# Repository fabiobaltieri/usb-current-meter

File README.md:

USB Current Meter
=================

This is a set of projects used to monitor the power used in an electrical
system using split core current sensors.

Project page on:

http://fabiobaltieri.com/2012/08/09/usb-current-meter/

License
-------

This program is free software: you can redistribute it and/or modify
it under the terms of the GNU General Public License as published by
the Free Software Foundation, either version 2 of the License, or
(at your option) any later version.

Contents
--------

    COPYING        text version of the GPL
    README         this file
    bootloader-8x/ source directory for 8x version bootloader
    commandline/   source directory for the commandline utility
    firmware*/     source directory for firmware files
    hardware/      source directory for the hardware design files
    rrd/           script and examples for usage with rrdtool

Firmware
--------

Building requires an avr-gcc toolchain, in the firmware/ directory, to build
run:

    make main.hex

Flashing the firmware on the device requires avrdude and a compatible hardware
programmer. Default configuration is stored at the beginning of the Makefile.
To program with the default configuration, run:

    make flash

Fuses can be configured running:

    make fuses

Hardware
--------

All hardware files (schematic, layout and libraries) are in CadSoft Eagle 6
format.

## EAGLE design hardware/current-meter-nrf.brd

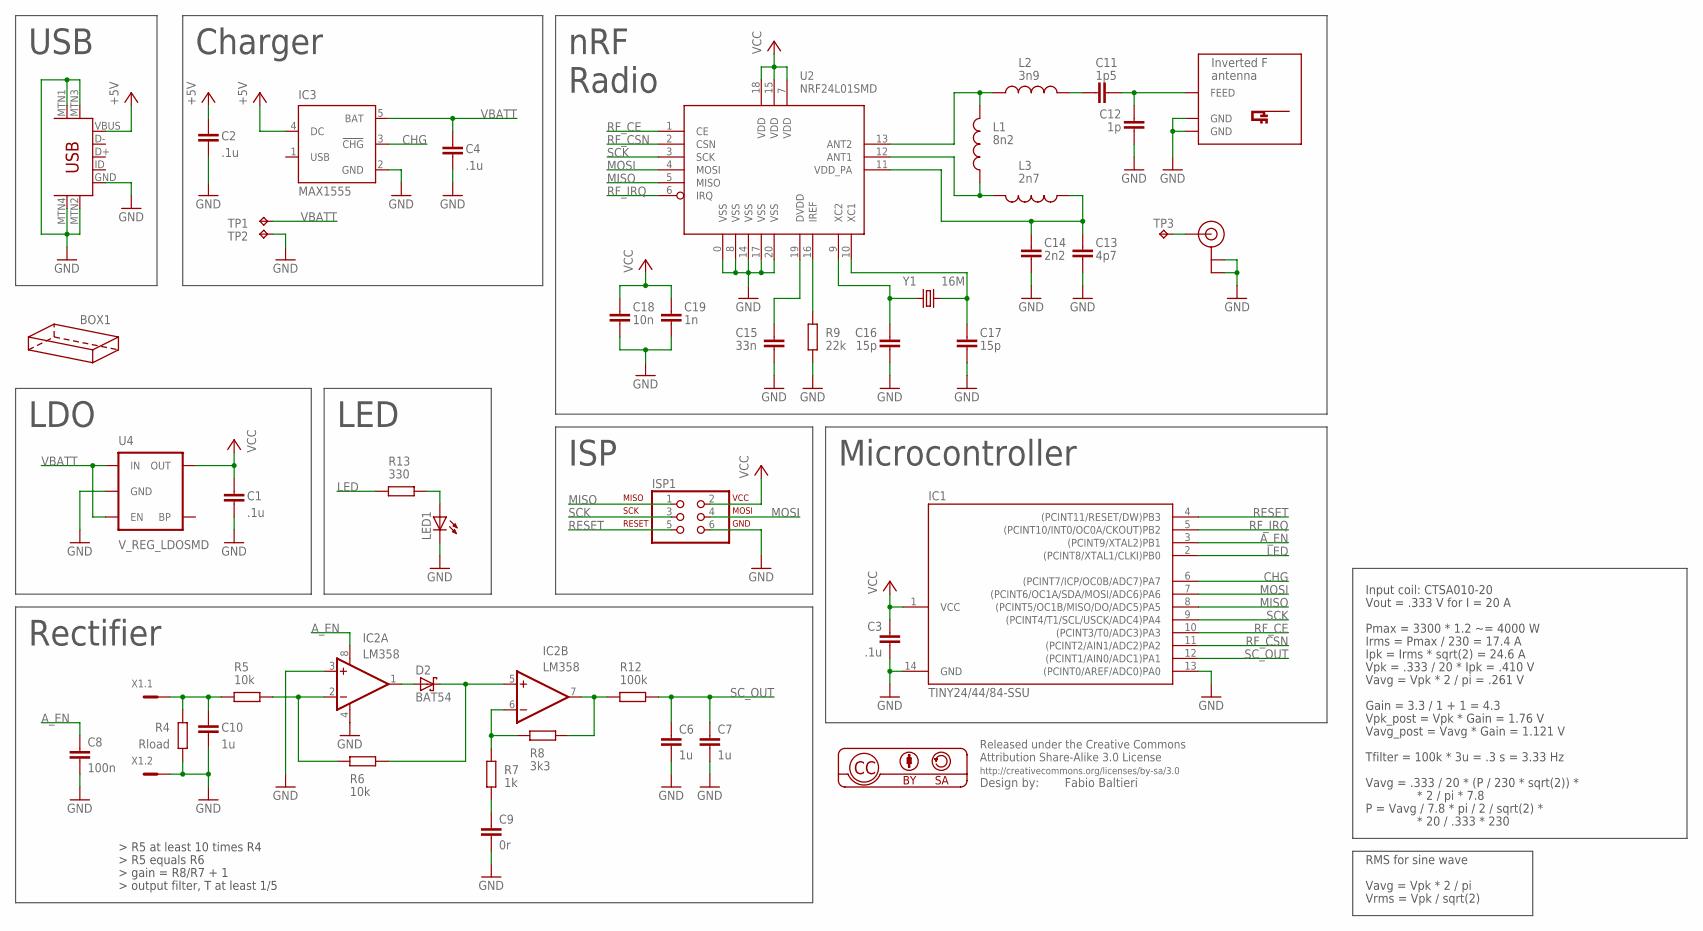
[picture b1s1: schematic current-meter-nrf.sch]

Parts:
BOX1: HAMMOND-BOX-G-1H; 1551G-1HOLE
C1, C2, C3, C4: .1u; C0805
C6, C7, C10: 1u; C0805
C8: 100n; C0805
C9: 0r; C0805
C11: 1p5; C0603
C12: 1p; C0603
C13: 4p7; C0603
C14: 2n2; C0603
C15: 33n; C0603
C16, C17: 15p; C0603
C18: 10n; C0603
C19: 1n; C0603
D2: BAT54; SOT23
IC1: TINY24/44/84-SSU; SOIC14
IC2: LM358; SO08
IC3: MAX1555; SOT23-5L
ISP1: ISP-AVR910PTH; 2X03
L1: 8n2; 0603
L2: 3n9; 0603
L3: 2n7; 0603
LED1: LEDSML0805; SML0805
R4: Rload; R0805
R5, R6: 10k; R0603
R7: 1k; R0603
R8: 3k3; R0603
R9: 22k; R0603
R12: 100k; R0603
R13: 330; R0603
TP1, TP2: TPTP12R; TP12R
TP3: TPTP08SQ; TP08SQ
U2: NRF24L01SMD; QFN20
U3: USB-MINIB-5PIN; USB-MINIB
U4: V_REG_LDOSMD; SOT23-5
U$1: INVERTED_F_ANTENNA+5; DN007+5
U$2: U.FL
X1: MC2
Y1: 16M; CRYSTAL-SMD-5X3

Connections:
+5V: C2.1, IC3.4 (DC), U3.VBUS
A_EN: C8.1, IC1.3 ((PCINT9/XTAL2)PB1), IC2.8 (V+)
CHG: IC1.6 ((PCINT7/ICP/OC0B/ADC7)PA7), IC3.3 (!CHG)
GND: C1.2, C2.2, C3.2, C4.2, C6.2, C7.2, C8.2, C9.2, C10.2, C12.2, C13.2, C14.2, C15.2, C16.2, C17.2, C18.2, C19.2, IC1.13 ((PCINT0/AREF/ADC0)PA0), IC1.14 (GND), IC2.3 (+IN), IC2.4 (V-), IC3.2 (GND), ISP1.6, LED1.C, R4.1, R9.2, TP2.TP, U2.0 (VSS), U2.8 (VSS), U2.14 (VSS), U2.17 (VSS), U2.20 (VSS), U3.GND, U3.MTN1 (MTN2), U3.MTN2 (MTN3), U3.MTN3 (MTN1), U3.MTN4, U4.2 (GND), U$1.GND, U$1.GND@1 (GND), U$2.P$1 (GND), U$2.P$2 (GND), X1.2
LED: IC1.2 ((PCINT8/XTAL1/CLKI)PB0), R13.2
MISO: IC1.8 ((PCINT5/OC1B/MISO/DO/ADC5)PA5), ISP1.1, U2.5 (MISO)
MOSI: IC1.7 ((PCINT6/OC1A/SDA/MOSI/ADC6)PA6), ISP1.4, U2.4 (MOSI)
unnamed: LED1.A, R13.1
unnamed: C9.1, R7.1
unnamed: L1.2, L3.2, U2.12 (ANT1)
unnamed: L1.1, L2.1, U2.13 (ANT2)
unnamed: IC2.2 (-IN), R5.2, R6.1
unnamed: D2.1 (A), IC2.1 (OUT)
unnamed: D2.3 (C), IC2.5 (+IN), R6.2
unnamed: C11.1, L2.2
unnamed: IC2.6 (-IN), R7.2, R8.1
unnamed: IC2.7 (OUT), R8.2, R12.1
unnamed: C11.2, C12.1, U$1.FEED
unnamed: C13.1, C14.1, L3.1, U2.11 (VDD_PA)
unnamed: C15.1, U2.19 (DVDD)
unnamed: R9.1, U2.16 (IREF)
unnamed: C17.1, U2.10 (XC1), Y1.3 (2)
unnamed: C16.1, U2.9 (XC2), Y1.1
unnamed: TP3.TP, U$2.P$3 (SIGNAL)
RESET: IC1.4 ((PCINT11/RESET/DW)PB3), ISP1.5
RF_CE: IC1.10 ((PCINT3/T0/ADC3)PA3), U2.1 (CE)
RF_CSN: IC1.11 ((PCINT2/AIN1/ADC2)PA2), U2.2 (CSN)
RF_IRQ: IC1.5 ((PCINT10/INT0/OC0A/CKOUT)PB2), U2.6 (IRQ)
SCK: IC1.9 ((PCINT4/T1/SCL/USCK/ADC4)PA4), ISP1.3, U2.3 (SCK)
SC_IN_A: C10.1, R4.2, R5.1, X1.1
SC_OUT: C6.1, C7.1, IC1.12 ((PCINT1/AIN0/ADC1)PA1), R12.2
VBATT: C4.1, IC3.5 (BAT), TP1.TP, U4.1 (IN), U4.3 (EN)
VCC: C1.1, C3.1, C18.1, C19.1, IC1.1 (VCC), ISP1.2, U2.7 (VDD), U2.15 (VDD), U2.18 (VDD), U4.5 (OUT)

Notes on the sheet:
USB
Microcontroller
ISP
LED
Rectifier
Pmax = 3300 * 1.2 ~= 4000 W
Irms = Pmax / 230 = 17.4 A
Ipk = Irms * sqrt(2) = 24.6 A
Vpk = .333 / 20 * Ipk = .410 V
Vout = .333 V for I = 20 A
Input coil: CTSA010-20
Vavg = Vpk * 2 / pi = .261 V
Gain = 3.3 / 1 + 1 = 4.3
Vpk_post = Vpk * Gain = 1.76 V
Vavg_post = Vavg * Gain = 1.121 V
RMS for sine wave
Vavg = Vpk * 2 / pi
Vrms = Vpk / sqrt(2)
Tfilter = 100k * 3u = .3 s = 3.33 Hz
Vavg = .333 / 20 * (P / 230 * sqrt(2)) *
* 2 / pi * 7.8
P = Vavg / 7.8 * pi / 2 / sqrt(2) *
* 20 / .333 * 230
nRF
Charger
Radio
LDO

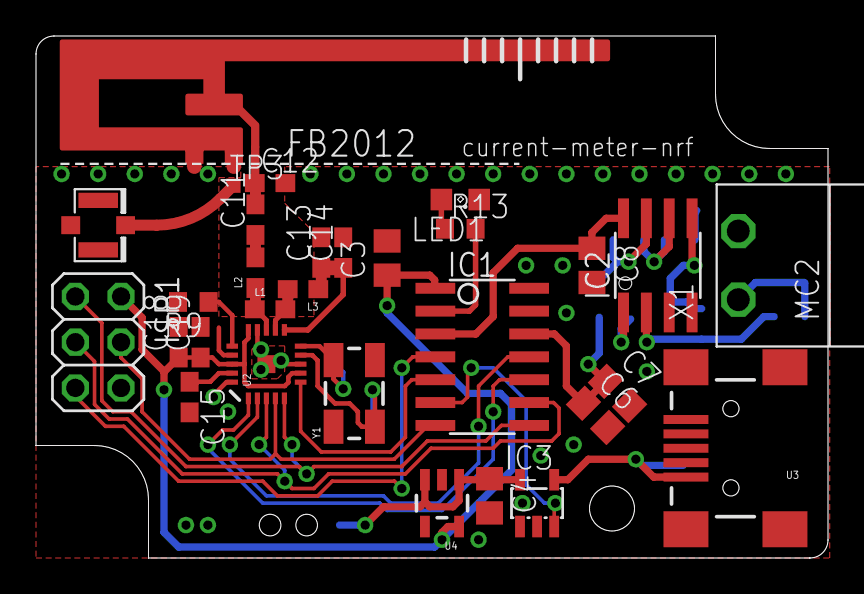
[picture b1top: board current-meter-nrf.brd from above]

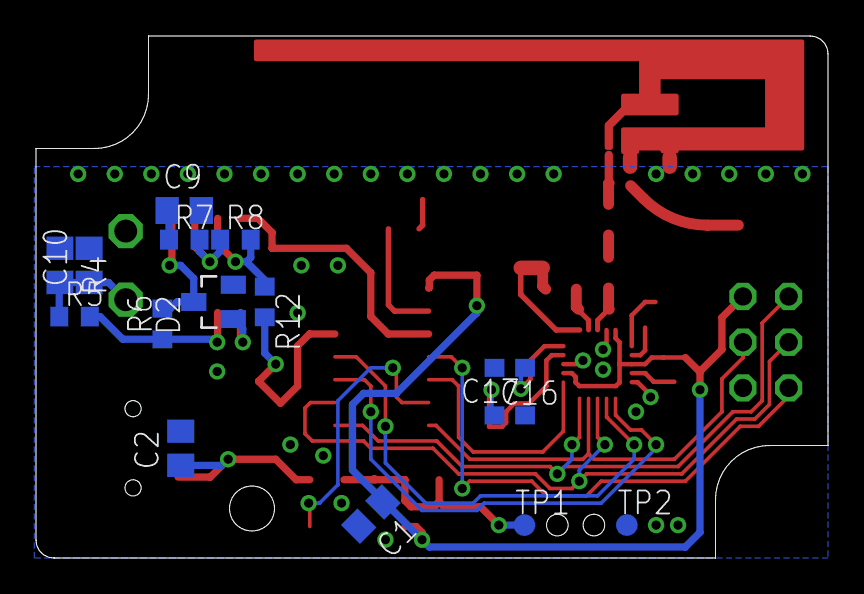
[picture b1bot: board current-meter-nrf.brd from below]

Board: 2 copper layers, 44.0 x 29.0 mm, 46 parts (15 on the bottom side), 33 nets.

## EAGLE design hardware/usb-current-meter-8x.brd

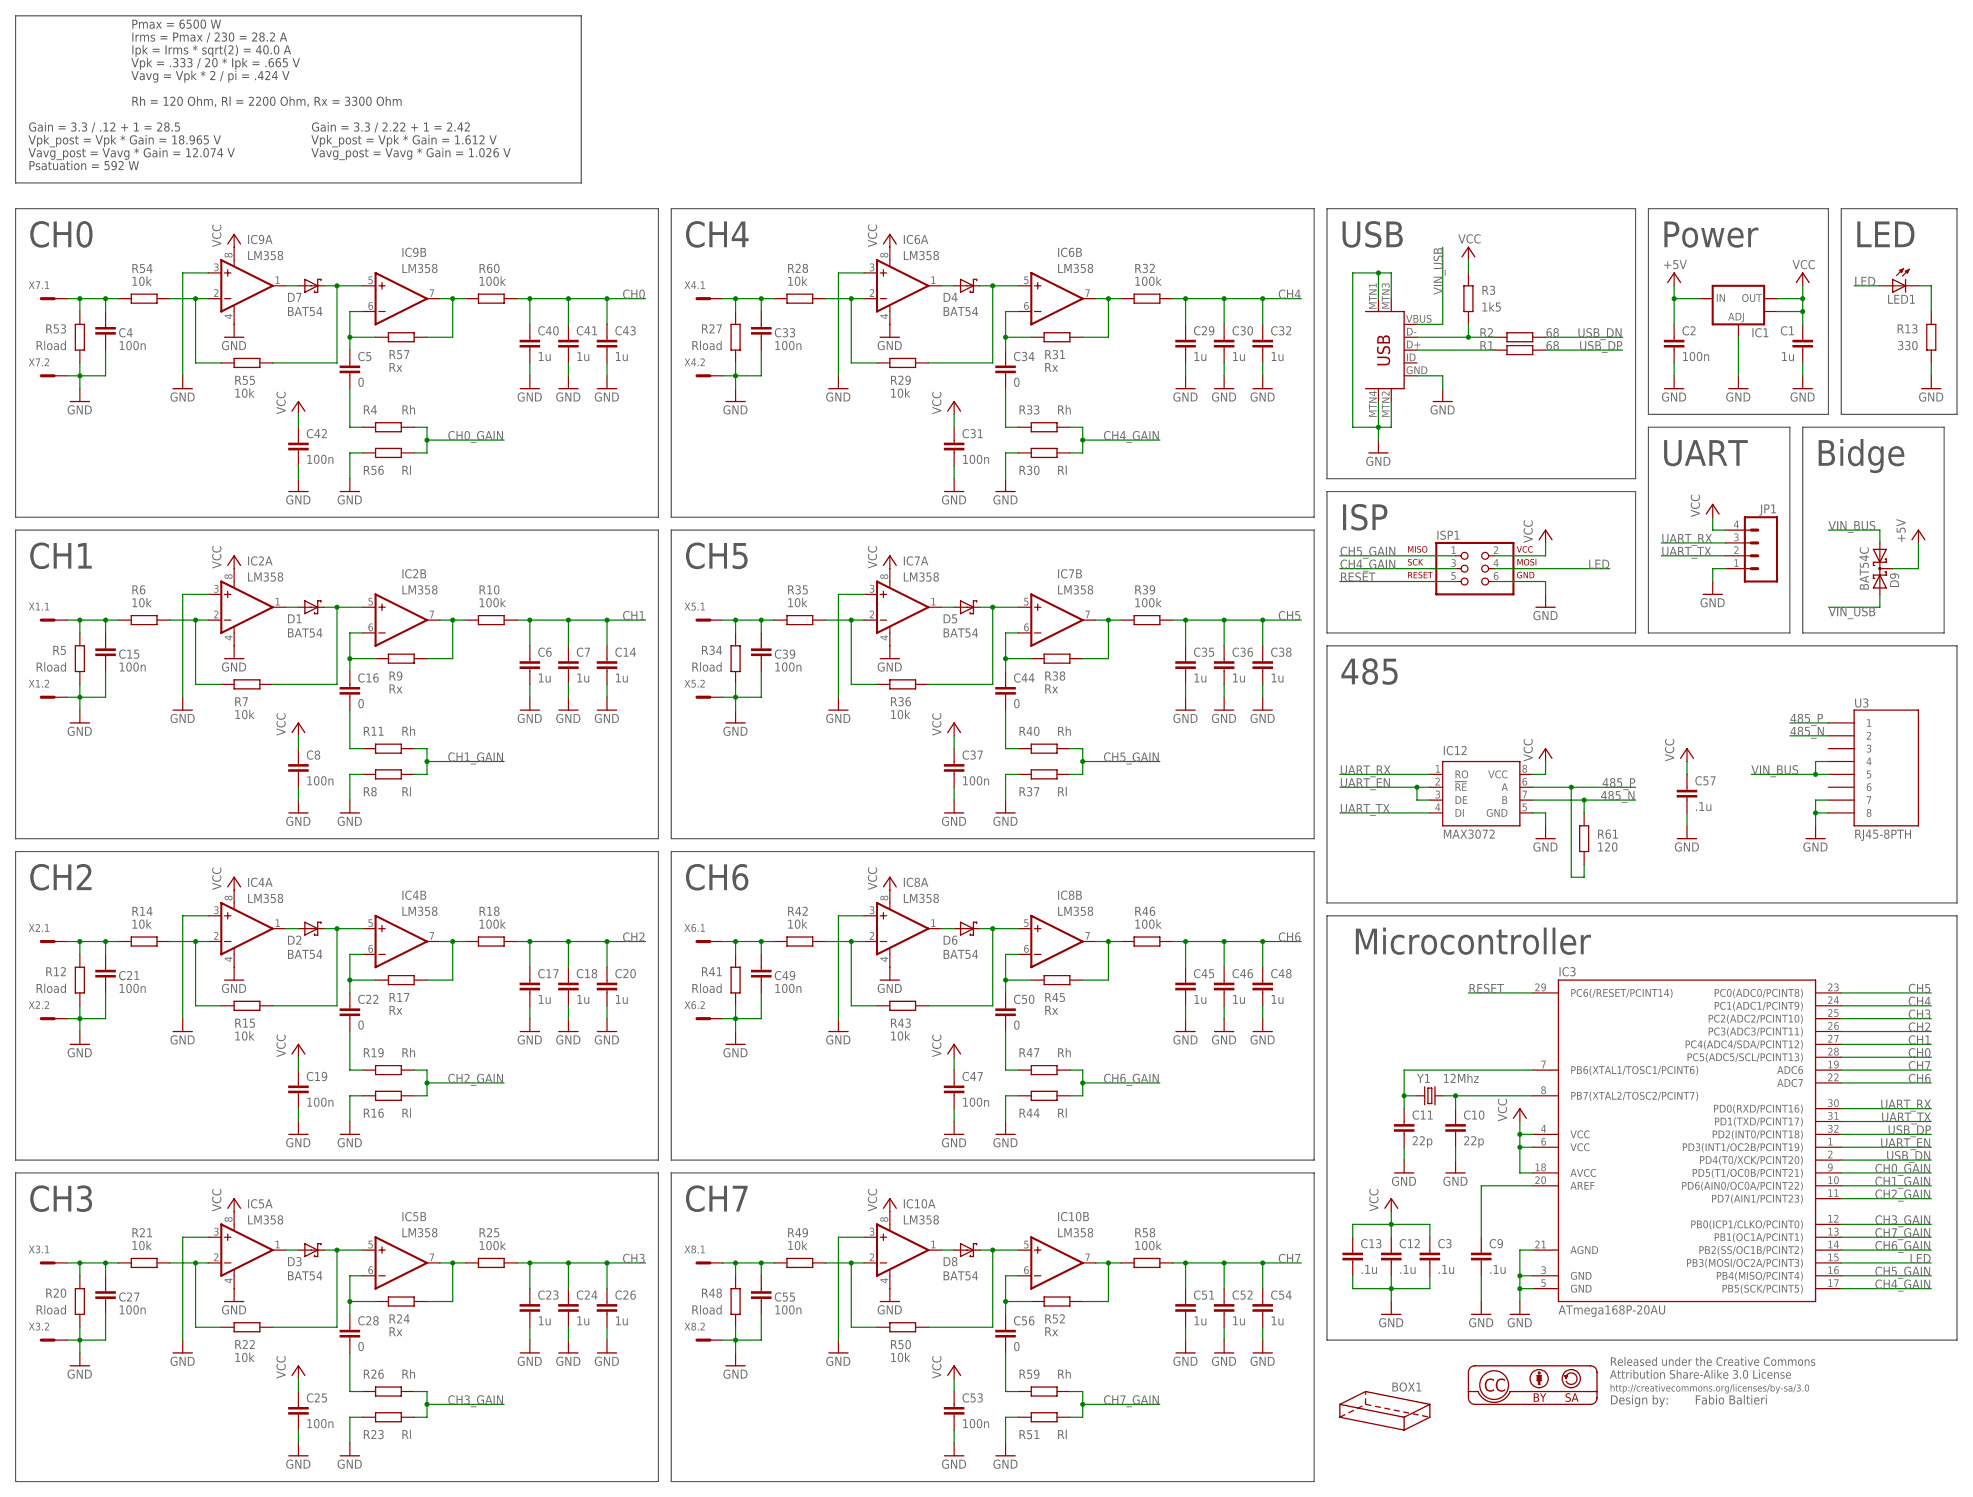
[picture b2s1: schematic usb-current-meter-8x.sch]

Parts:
BOX1: HAMMOND-BOX-XXA; 1591XXA
C1, C6, C7, C14, C17, C18, C20, C23, C24, C26, C29, C30, C32, C35, C36, C38, C40, C41, C43, C45, C46, C48, C51, C52, C54: 1u; C0805
C2, C4, C8, C15, C19, C21, C25, C27, C31, C33, C37, C39, C42, C47, C49, C53, C55: 100n; C0805
C3, C9, C12, C13, C57: .1u; C0805
C5, C16, C22, C28, C34, C44, C50, C56: 0; C0805
C10, C11: 22p; C0805
D1, D2, D3, D4, D5, D6, D7, D8: BAT54; SOT23
D9: BAT54C; SOT23
IC1: V_REG_LM1117SOT223; SOT223
IC2, IC4, IC5, IC6, IC7, IC8, IC9, IC10: LM358; SO08
IC3: ATmega168P-20AU; TQFP32-08
IC12: MAX3072; SOIC8
ISP1: ISP-AVR910PTH; 2X03
JP1: M04PTH; 1X04
LED1: LEDSML0805; SML0805
R1, R2: 68; R0603
R3: 1k5; R0603
R4, R11, R19, R26, R33, R40, R47, R59: Rh; R0603
R5, R12, R20, R27, R34, R41, R48, R53: Rload; R0805
R6, R7, R14, R15, R21, R22, R28, R29, R35, R36, R42, R43, R49, R50, R54, R55: 10k; R0603
R8, R16, R23, R30, R37, R44, R51, R56: Rl; R0603
R9, R17, R24, R31, R38, R45, R52, R57: Rx; R0603
R10, R18, R25, R32, R39, R46, R58, R60: 100k; R0603
R13: 330; R0603
R61: 120; R0603
U3: RJ45-8PTH; RJ45-8
U$1: USB-MINIB-5PIN; USB-MINIB
U$2: Fabio Baltieri; CREATIVE_COMMONS
X1, X2, X3, X4, X5, X6, X7, X8: MC2
Y1: 12Mhz; HC49U-V

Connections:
485_N: IC12.7 (B), R61.1, U3.2
485_P: IC12.6 (A), R61.2, U3.1
+5V: C2.1, D9.3 (CC), IC1.3 (IN)
CH0: C40.1, C41.1, C43.1, IC3.28 (PC5(ADC5/SCL/PCINT13)), R60.2
CH0_GAIN: IC3.9 (PD5(T1/OC0B/PCINT21)), R4.1, R56.2
CH0_IN: C4.1, R53.2, R54.1, X7.1
CH0_IN1: C15.1, R5.2, R6.1, X1.1
CH0_IN2: C21.1, R12.2, R14.1, X2.1
CH0_IN3: C33.1, R27.2, R28.1, X4.1
CH0_IN4: C39.1, R34.2, R35.1, X5.1
CH0_IN5: C55.1, R48.2, R49.1, X8.1
CH0_IN6: C27.1, R20.2, R21.1, X3.1
CH0_IN8: C49.1, R41.2, R42.1, X6.1
CH1: C6.1, C7.1, C14.1, IC3.27 (PC4(ADC4/SDA/PCINT12)), R10.2
CH1_GAIN: IC3.10 (PD6(AIN0/OC0A/PCINT22)), R8.2, R11.1
CH2: C17.1, C18.1, C20.1, IC3.26 (PC3(ADC3/PCINT11)), R18.2
CH2_GAIN: IC3.11 (PD7(AIN1/PCINT23)), R16.2, R19.1
CH3: C23.1, C24.1, C26.1, IC3.25 (PC2(ADC2/PCINT10)), R25.2
CH3_GAIN: IC3.12 (PB0(ICP1/CLKO/PCINT0)), R23.2, R26.1
CH4: C29.1, C30.1, C32.1, IC3.24 (PC1(ADC1/PCINT9)), R32.2
CH4_GAIN: IC3.17 (PB5(SCK/PCINT5)), ISP1.3, R30.2, R33.1
CH5: C35.1, C36.1, C38.1, IC3.23 (PC0(ADC0/PCINT8)), R39.2
CH5_GAIN: IC3.16 (PB4(MISO/PCINT4)), ISP1.1, R37.2, R40.1
CH6: C45.1, C46.1, C48.1, IC3.22 (ADC7), R46.2
CH6_GAIN: IC3.14 (PB2(SS/OC1B/PCINT2)), R44.2, R47.1
CH7: C51.1, C52.1, C54.1, IC3.19 (ADC6), R58.2
CH7_GAIN: IC3.13 (PB1(OC1A/PCINT1)), R51.2, R59.1
GND: C1.2, C2.2, C3.2, C4.2, C6.2, C7.2, C8.2, C9.2, C10.2, C11.2, C12.2, C13.2, C14.2, C15.2, C17.2, C18.2, C19.2, C20.2, C21.2, C23.2, C24.2, C25.2, C26.2, C27.2, C29.2, C30.2, C31.2, C32.2, C33.2, C35.2, C36.2, C37.2, C38.2, C39.2, C40.2, C41.2, C42.2, C43.2, C45.2, C46.2, C47.2, C48.2, C49.2, C51.2, C52.2, C53.2, C54.2, C55.2, C57.2, IC1.1 (ADJ), IC2.3 (+IN), IC2.4 (V-), IC3.3 (GND), IC3.5 (GND), IC3.21 (AGND), IC4.3 (+IN), IC4.4 (V-), IC5.3 (+IN), IC5.4 (V-), IC6.3 (+IN), IC6.4 (V-), IC7.3 (+IN), IC7.4 (V-), IC8.3 (+IN), IC8.4 (V-), IC9.3 (+IN), IC9.4 (V-), IC10.3 (+IN), IC10.4 (V-), IC12.5 (GND), ISP1.6, JP1.1, R5.1, R8.1, R12.1, R13.1, R16.1, R20.1, R23.1, R27.1, R30.1, R34.1, R37.1, R41.1, R44.1, R48.1, R51.1, R53.1, R56.1, U3.7, U3.8, U$1.GND, U$1.MTN1 (MTN2), U$1.MTN2 (MTN3), U$1.MTN3 (MTN1), U$1.MTN4, X1.2, X2.2, X3.2, X4.2, X5.2, X6.2, X7.2, X8.2
LED: IC3.15 (PB3(MOSI/OC2A/PCINT3)), ISP1.4, LED1.A
unnamed: R2.1, R3.1, U$1.D-
unnamed: R1.1, U$1.D+
unnamed: LED1.C, R13.2
unnamed: C11.1, IC3.7 (PB6(XTAL1/TOSC1/PCINT6)), Y1.1
unnamed: C10.1, IC3.8 (PB7(XTAL2/TOSC2/PCINT7)), Y1.2
unnamed: C9.1, IC3.20 (AREF)
unnamed: C5.2, R4.2
unnamed: IC2.2 (-IN), R6.2, R7.1
unnamed: D1.1 (A), IC2.1 (OUT)
unnamed: D1.3 (C), IC2.5 (+IN), R7.2
unnamed: C16.1, IC2.6 (-IN), R9.1
unnamed: IC2.7 (OUT), R9.2, R10.1
unnamed: C16.2, R11.2
unnamed: IC4.2 (-IN), R14.2, R15.1
unnamed: D2.1 (A), IC4.1 (OUT)
unnamed: D2.3 (C), IC4.5 (+IN), R15.2
unnamed: C22.1, IC4.6 (-IN), R17.1
unnamed: IC4.7 (OUT), R17.2, R18.1
unnamed: C22.2, R19.2
unnamed: IC6.2 (-IN), R28.2, R29.1
unnamed: D4.1 (A), IC6.1 (OUT)
unnamed: D4.3 (C), IC6.5 (+IN), R29.2
unnamed: C34.1, IC6.6 (-IN), R31.1
unnamed: IC6.7 (OUT), R31.2, R32.1
unnamed: C34.2, R33.2
unnamed: IC7.2 (-IN), R35.2, R36.1
unnamed: D5.1 (A), IC7.1 (OUT)
unnamed: D5.3 (C), IC7.5 (+IN), R36.2
unnamed: C44.1, IC7.6 (-IN), R38.1
unnamed: IC7.7 (OUT), R38.2, R39.1
unnamed: C44.2, R40.2
unnamed: IC10.2 (-IN), R49.2, R50.1
unnamed: D8.1 (A), IC10.1 (OUT)
unnamed: D8.3 (C), IC10.5 (+IN), R50.2
unnamed: C56.1, IC10.6 (-IN), R52.1
unnamed: IC10.7 (OUT), R52.2, R58.1
unnamed: IC9.2 (-IN), R54.2, R55.1
unnamed: D7.1 (A), IC9.1 (OUT)
unnamed: D7.3 (C), IC9.5 (+IN), R55.2
unnamed: C5.1, IC9.6 (-IN), R57.1
unnamed: IC9.7 (OUT), R57.2, R60.1
unnamed: C56.2, R59.2
unnamed: IC5.2 (-IN), R21.2, R22.1
unnamed: D3.1 (A), IC5.1 (OUT)
unnamed: D3.3 (C), IC5.5 (+IN), R22.2
unnamed: C28.1, IC5.6 (-IN), R24.1
unnamed: IC5.7 (OUT), R24.2, R25.1
unnamed: C28.2, R26.2
unnamed: IC8.2 (-IN), R42.2, R43.1
unnamed: D6.1 (A), IC8.1 (OUT)
unnamed: D6.3 (C), IC8.5 (+IN), R43.2
unnamed: C50.1, IC8.6 (-IN), R45.1
unnamed: IC8.7 (OUT), R45.2, R46.1
unnamed: C50.2, R47.2
RESET: IC3.29 (PC6(/RESET/PCINT14)), ISP1.5
UART_EN: IC3.1 (PD3(INT1/OC2B/PCINT19)), IC12.2 (!RE), IC12.3 (DE)
UART_RX: IC3.30 (PD0(RXD/PCINT16)), IC12.1 (RO), JP1.3
UART_TX: IC3.31 (PD1(TXD/PCINT17)), IC12.4 (DI), JP1.2
USB_DN: IC3.2 (PD4(T0/XCK/PCINT20)), R2.2
USB_DP: IC3.32 (PD2(INT0/PCINT18)), R1.2
VCC: C1.1, C3.1, C8.1, C12.1, C13.1, C19.1, C25.1, C31.1, C37.1, C42.1, C47.1, C53.1, C57.1, IC1.2 (OUT), IC1.4 (OUT), IC2.8 (V+), IC3.4 (VCC), IC3.6 (VCC), IC3.18 (AVCC), IC4.8 (V+), IC5.8 (V+), IC6.8 (V+), IC7.8 (V+), IC8.8 (V+), IC9.8 (V+), IC10.8 (V+), IC12.8 (VCC), ISP1.2, JP1.4, R3.2
VIN_BUS: D9.1 (A1), U3.4, U3.5
VIN_USB: D9.2 (A2), U$1.VBUS

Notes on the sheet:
USB
Power
Microcontroller
ISP
LED
CH0
UART
CH1
CH2
CH3
CH4
CH5
CH6
CH7
485
Bidge
Pmax = 6500 W
Irms = Pmax / 230 = 28.2 A
Ipk = Irms * sqrt(2) = 40.0 A
Vpk = .333 / 20 * Ipk = .665 V
Vavg = Vpk * 2 / pi = .424 V
Gain = 3.3 / .12 + 1 = 28.5
Vpk_post = Vpk * Gain = 18.965 V
Vavg_post = Vavg * Gain = 12.074 V
Rh = 120 Ohm, Rl = 2200 Ohm, Rx = 3300 Ohm
Gain = 3.3 / 2.22 + 1 = 2.42
Vpk_post = Vpk * Gain = 1.612 V
Vavg_post = Vavg * Gain = 1.026 V
Psatuation = 592 W

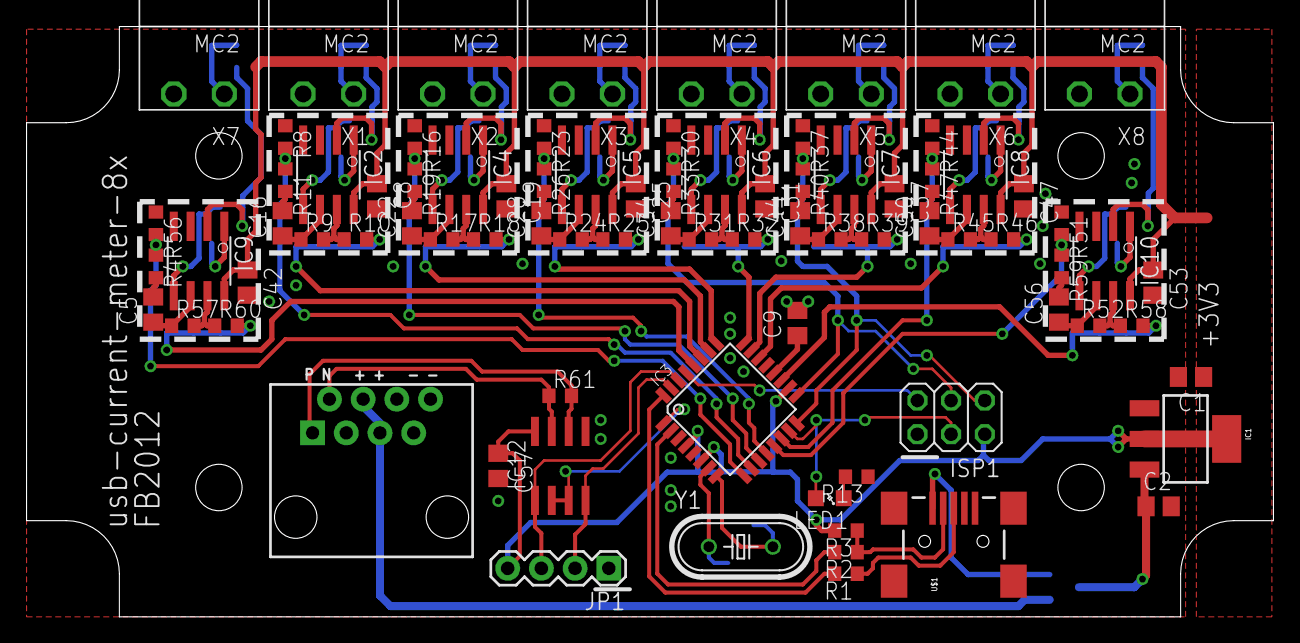
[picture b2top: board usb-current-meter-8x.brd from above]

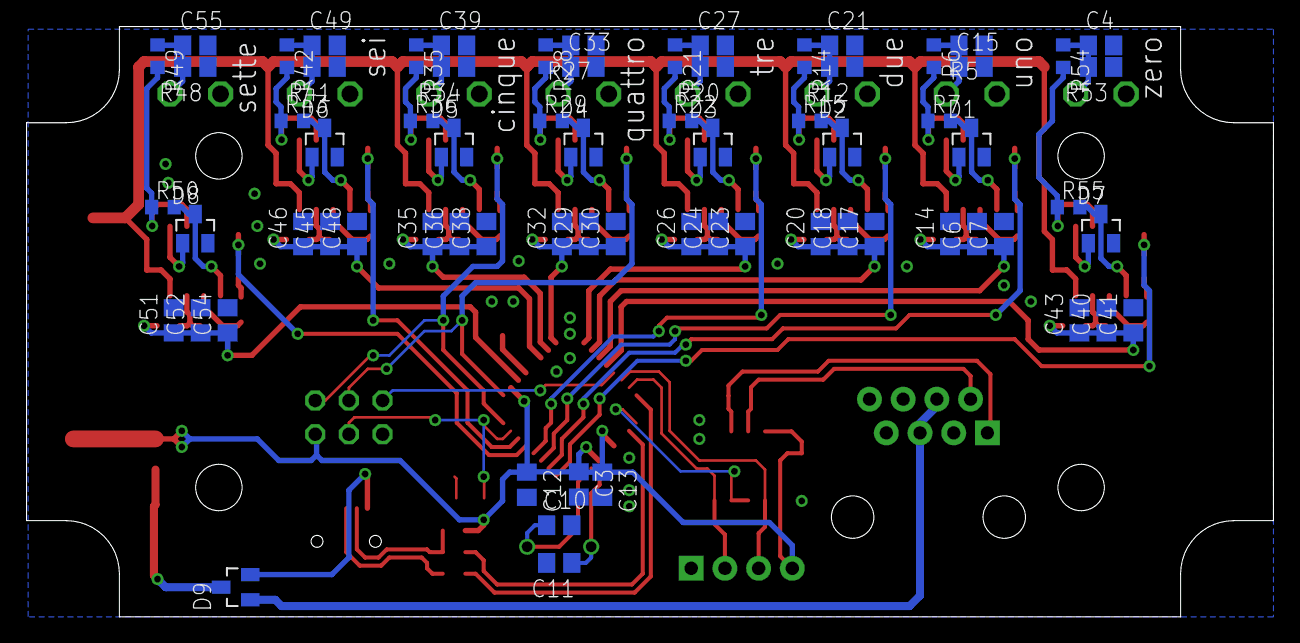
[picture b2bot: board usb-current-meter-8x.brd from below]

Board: 2 copper layers, 94.0 x 44.5 mm, 154 parts (70 on the bottom side), 92 nets.

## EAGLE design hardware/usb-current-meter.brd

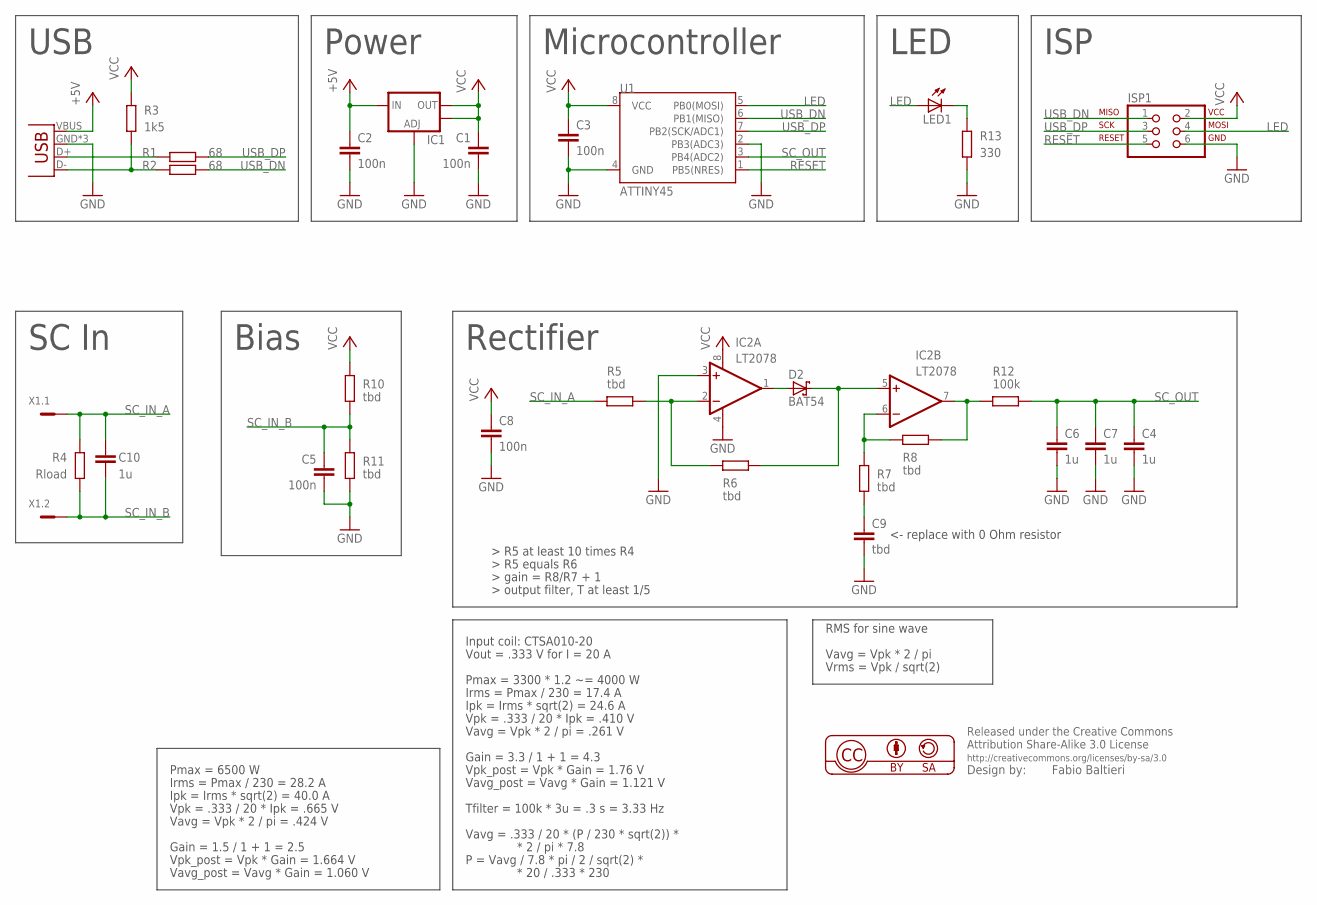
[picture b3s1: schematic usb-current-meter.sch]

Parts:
C1, C2, C3, C5, C8: 100n; C0805
C4, C6, C7, C10: 1u; C0805
C9: tbd; C0805
D2: BAT54; SOT23
IC1: V_REG_LM1117SOT223; SOT223
IC2: LT2078; SO08
ISP1: ISP-AVR910; 2X03_BORDER_TP
LED1: LEDSML0805; SML0805
R1, R2: 68; R0603
R3: 1k5; R0603
R4: Rload; R0805
R5, R6, R7, R8, R10, R11: tbd; R0603
R12: 100k; R0603
R13: 330; R0603
U1: ATTINY45; SO08-EIAJ
X1: MC2
X3: USB-A-H

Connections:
+5V: C2.1, IC1.3 (IN), X3.VBUS (GND)
GND: C1.2, C2.2, C3.2, C4.2, C5.2, C6.2, C7.2, C8.2, C9.2, IC1.1 (ADJ), IC2.3 (+IN), IC2.4 (V-), ISP1.6, R11.1, R13.1, U1.2 (PB3(ADC3)), U1.4 (GND), X3.GND (VBUS), X3.GND2 (VBUS), X3.GND3 (VBUS)
LED: ISP1.4, LED1.A, U1.5 (PB0(MOSI))
unnamed: R2.1, R3.1, X3.D- (D+)
unnamed: R1.1, X3.D+ (D-)
unnamed: LED1.C, R13.2
unnamed: C9.1, R7.1
unnamed: IC2.2 (-IN), R5.2, R6.1
unnamed: D2.1 (A), IC2.1 (OUT)
unnamed: D2.3 (C), IC2.5 (+IN), R6.2
unnamed: IC2.6 (-IN), R7.2, R8.1
unnamed: IC2.7 (OUT), R8.2, R12.1
RESET: ISP1.5, U1.1 (PB5(NRES))
SC_IN_A: C10.1, R4.2, R5.1, X1.1
SC_IN_B: C5.1, C10.2, R4.1, R10.1, R11.2, X1.2
SC_OUT: C4.1, C6.1, C7.1, R12.2, U1.3 (PB4(ADC2))
USB_DN: ISP1.1, R2.2, U1.6 (PB1(MISO))
USB_DP: ISP1.3, R1.2, U1.7 (PB2(SCK/ADC1))
VCC: C1.1, C3.1, C8.1, IC1.2 (OUT), IC1.4 (OUT), IC2.8 (V+), ISP1.2, R3.2, R10.2, U1.8 (VCC)

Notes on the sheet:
USB
Power
Microcontroller
ISP
LED
SC In
Rectifier
Bias
Pmax = 3300 * 1.2 ~= 4000 W
Irms = Pmax / 230 = 17.4 A
Ipk = Irms * sqrt(2) = 24.6 A
Vpk = .333 / 20 * Ipk = .410 V
Vout = .333 V for I = 20 A
Input coil: CTSA010-20
Vavg = Vpk * 2 / pi = .261 V
Gain = 3.3 / 1 + 1 = 4.3
Vpk_post = Vpk * Gain = 1.76 V
Vavg_post = Vavg * Gain = 1.121 V
RMS for sine wave
Vavg = Vpk * 2 / pi
Vrms = Vpk / sqrt(2)
Tfilter = 100k * 3u = .3 s = 3.33 Hz
Vavg = .333 / 20 * (P / 230 * sqrt(2)) *
* 2 / pi * 7.8
P = Vavg / 7.8 * pi / 2 / sqrt(2) *
* 20 / .333 * 230
Pmax = 6500 W
Irms = Pmax / 230 = 28.2 A
Ipk = Irms * sqrt(2) = 40.0 A
Vpk = .333 / 20 * Ipk = .665 V
Vavg = Vpk * 2 / pi = .424 V
Gain = 1.5 / 1 + 1 = 2.5
Vpk_post = Vpk * Gain = 1.664 V
Vavg_post = Vavg * Gain = 1.060 V
<- replace with 0 Ohm resistor

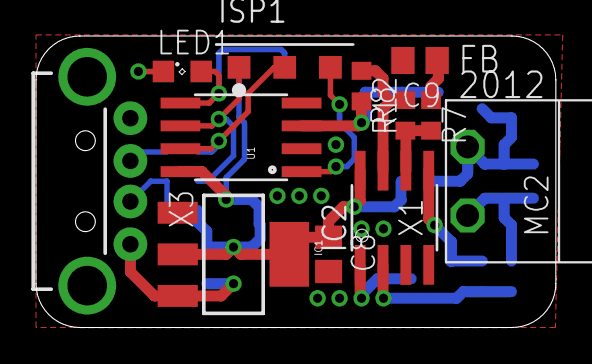
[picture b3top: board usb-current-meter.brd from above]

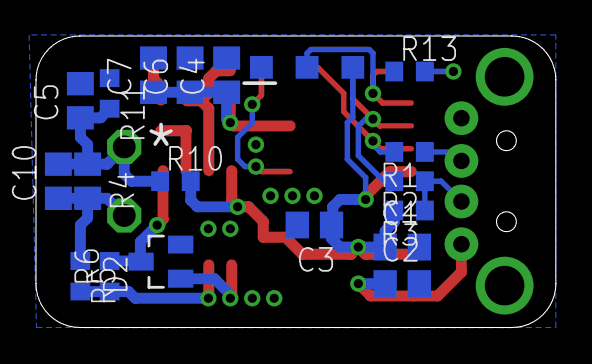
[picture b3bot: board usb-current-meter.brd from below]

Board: 2 copper layers, 28.9 x 16.2 mm, 30 parts (18 on the bottom side), 19 nets.

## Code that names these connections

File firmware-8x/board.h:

/* LEDs */

#define LED_A_PORT    PORTB
#define LED_A_DDR     DDRB
#define LED_A         PB3

#define led_a_on()     LED_A_PORT |=  _BV(LED_A);
#define led_a_off()    LED_A_PORT &= ~_BV(LED_A);
#define led_a_toggle() LED_A_PORT ^=  _BV(LED_A);

#define led_init() do {				\
		LED_A_DDR |= _BV(LED_A);	\
	} while (0);

/* ADC */
#define AMP_TH_H 550
#define AMP_TH_L 500
#define ADC_VREF_mV (1100 / 4)
#define ADC_VREF_BITS (1024 / 4)

/* 6500W version */
#define CAL_POWER	6500
#define CAL_VOLTAGE_L	1026l
#define CAL_VOLTAGE_H	12074l

/* Gains */
#define set_high_gain_ch0()	(DDRD |=  _BV(PD5))
#define set_low_gain_ch0()	(DDRD &= ~_BV(PD5))

#define set_high_gain_ch1()	(DDRD |=  _BV(PD6))
#define set_low_gain_ch1()	(DDRD &= ~_BV(PD6))

#define set_high_gain_ch2()	(DDRD |=  _BV(PD7))
#define set_low_gain_ch2()	(DDRD &= ~_BV(PD7))

#define set_high_gain_ch3()	(DDRB |=  _BV(PB0))
#define set_low_gain_ch3()	(DDRB &= ~_BV(PB0))

#define set_high_gain_ch4()	(DDRB |=  _BV(PB5))
#define set_low_gain_ch4()	(DDRB &= ~_BV(PB5))

#define set_high_gain_ch5()	(DDRB |=  _BV(PB4))
#define set_low_gain_ch5()	(DDRB &= ~_BV(PB4))

#define set_high_gain_ch6()	(DDRB |=  _BV(PB2))
#define set_low_gain_ch6()	(DDRB &= ~_BV(PB2))

#define set_high_gain_ch7()	(DDRB |=  _BV(PB1))
#define set_low_gain_ch7()	(DDRB &= ~_BV(PB1))

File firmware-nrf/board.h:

/* LEDs */
#define LED_A_PORT    PORTB
#define LED_A_DDR     DDRB
#define LED_A         PB0

#define led_a_on()     LED_A_PORT |=  _BV(LED_A);
#define led_a_off()    LED_A_PORT &= ~_BV(LED_A);
#define led_a_toggle() LED_A_PORT ^=  _BV(LED_A);

#define led_init() do {				\
		LED_A_DDR |= _BV(LED_A);	\
	} while (0);

/* SPI */
#define SPI_DDR  DDRA
#define SPI_PORT PORTA
#define SPI_PIN  PINA
#define SPI_SS   PA2
#define SPI_SCK  PA4
#define SPI_MISO PA5
#define SPI_MOSI PA6

/* Charger */
#define CHG_PORT	PORTA
#define CHG_PIN		PINA
#define CHG		PA7

#define chg_init()	do { CHG_PORT |= _BV(CHG); } while (0)
#define is_charging()	(!(PINA & _BV(PA7)))

/* nRF24L01+ SPI */
#define NRF_DDR  DDRA
#define NRF_PORT PORTA
#define NRF_CS   SPI_SS
#define NRF_CE   PA3

#define nrf_cs_h() (NRF_PORT |=  _BV(NRF_CS))
#define nrf_cs_l() (NRF_PORT &= ~_BV(NRF_CS))
#define nrf_ce_h() (NRF_PORT |=  _BV(NRF_CE))
#define nrf_ce_l() (NRF_PORT &= ~_BV(NRF_CE))

/* Analog */
#define ANALOG_PORT    PORTB
#define ANALOG_DDR     DDRB
#define ANALOG         PB1

#define analog_on()     ANALOG_PORT |=  _BV(ANALOG);
#define analog_off()    ANALOG_PORT &= ~_BV(ANALOG);

#define analog_init() do {			\
		ANALOG_DDR |= _BV(ANALOG);	\
	} while (0);

/* ADC */
#define ADC_COIL       (_BV(REFS1) | 0x01)
#define ADC_OFFSET_20X (_BV(REFS1) | 0x23)
#define ADC_COIL_1X    (_BV(REFS1) | 0x28)
#define ADC_COIL_20X   (_BV(REFS1) | 0x29)
#define ADC_VCC        (0x21)

#define AMP_TH 45 /* ~ 1024 / 20 */
#define ADC_VREF_mV (1100 / 4)
#define ADC_VREF_BITS (1024 / 4)

/* 4000W version */
#define CAL_POWER	4000
#define CAL_VOLTAGE	1121l
/* 6500W version */
//#define CAL_POWER	6500
//#define CAL_VOLTAGE	1060l
/* 12000W version */
//#define CAL_POWER	(12000 / 10)
//#define CAL_VOLTAGE	(1020l / 10)

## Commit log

2012-01-21 hardware: initial commit, rev0
2012-01-23 hardware: add 8x schematic
2012-01-23 hardware: first version with 1 module
2012-01-23 hardware: progress save
2012-01-24 hardware: add license, silkscreen
2012-02-11 hardware: add some filtering capacitors
2012-02-13 docs: add ctsa010 and dent 20a datasheets
2012-02-13 hardware: update variants, add notes
2012-03-03 firmware: add clean 20120109 usbdrv lib sources
2012-03-03 firmware: add initial Makefile
2012-03-03 firmware: clean up of vusb files
2012-03-03 firmware: add example requests.h
2012-03-03 firmware: add default usbconfig.h
2012-03-03 main: add reset_cpu request
2012-03-03 firmware: clean configuration for ATtiny85
2012-03-03 main: remove typedef to usbRequest
2012-03-03 usbconfig: change vendor/product strings
2012-03-24 firmware: initial current-meter firmware
2012-03-24 firmware: move get_power in a separate function
2012-03-24 firmware: add in-firmware W conversion
2012-03-24 firmware: add GET_RAW request
2012-03-26 commandline: add commandline utility
2012-03-27 commandline: add control message error check
2012-03-27 commandline: add divisor parameter
2012-03-27 commandline: add send_reset function
2012-03-27 hardware: add calculations for 6.5kW full-scale
2012-03-27 gitignore: add gitignore file
2012-03-28 firmware: power down analog pins digiatal logic
2012-03-28 hardware: 8x schematic updated
2012-03-30 hardware: re-made calculations for 230V (welcome to 2012)
2012-03-30 firmware: use new scaler for 230V
2012-03-31 8x: progress save
2012-03-31 firmware: adc: do not use ADC sleep mode
2012-03-31 firwmare: adc: remove now unused empty ADC isr
2012-03-31 firmware: add auto sampling mode
2012-03-31 cmdline: add auto sampling flag
2012-03-31 commandline: add voltage scale option
2012-03-31 commandline: rewrite help section
2012-03-31 commandline: better rrdtool integration
2012-03-31 commandline: add daemonize option
2012-03-31 commandline: change set_mode option behaviour
2012-03-31 commandline: background only in rrdtool mode
2012-03-31 commandline: cosmetic changes
2012-03-31 firmware: board.h: prepare macro for 6kW version
2012-03-31 firmware: remove unuseful saturation_th
2012-03-31 firmware: adc: turn on bandgap during init
2012-03-31 firmware: rework arithmetic to get better precision
2012-03-31 commandline: big endian support
2012-04-01 firmware: fix div_round macro
2012-04-10 rrd: add create and graph scripts
2012-04-10 docs: add bc script used to get gain resistor values
2012-04-21 firmware: change Vref, new values
2012-04-21 hardware: change values for use with 1.1Vref
2012-06-14 8x: moved usb connector into the board
2012-06-14 8x: remove old reference shapes
2012-06-14 hw: move low-side connector .6mm out
2012-06-14 hw: 8x: add silk
2012-06-14 hw: add current-meter-nrf
2012-06-14 hw: cosmetic refactor
2012-06-14 hw: nrf: progress save
2012-06-14 nrf: hw: progress save
2012-07-24 hw: 8x: add part numbers
2012-08-20 hw: nrf: add missing part value
2012-08-22 fw: add initial nrf firmware
2012-08-22 fw: nrf: add adc support
2012-08-22 fw: nrf: add vcc measure support
2012-08-22 fw: nrf: add spi write optimized function
2012-08-22 fw: nrf: use optimized write in nrf
2012-08-31 Makefile: remove redundant -Os
2012-08-31 fw-nrf: fix wrong adc channels
2012-08-31 fw-nrf: add get_power function
2012-08-31 fw-nrf: use get_power, add debug print
2012-09-01 bootloader-8x: add bootloader for 8x hardware
2012-09-02 gitignore: ignore .d files globally
2012-09-02 fw-nrf: add board id files
2012-09-02 main: use nrf_frame
2012-09-08 hw: change opamp to lt2078
2012-09-08 add COPYING and README files
2012-09-08 hw: add pdf schematics
2012-09-08 README: add blog link
2012-09-08 fw-nrf: update nrf packet format change
2012-09-08 Makefile: let the linker drop unused functions
2012-09-10 nw-nrf: change default fuses
2012-09-11 fw: adc: rise settle time to 70us
2012-09-15 fw: increase stabilization delay to 200us
2012-09-15 fw-nrf: increase stabilization delay to 200us
2012-09-15 fw-8x: add first 8x firmware
2012-09-15 cmdline-8x: add initial commandline-8x utility
2012-09-15 hw: 8x: clean up schematics, add calcs
2012-11-07 fw: usbdrv: add const on PROGMEM lines
2012-11-07 fw-8x: cosmetic fix
2012-11-07 fw-8x: upgrade usbdrv for new gcc
2012-11-08 bl-8x: update for gcc 4.7
2012-11-08 bl-8x: fix minor warning
2012-11-09 fw-8x: remove statement with no effect
2012-11-09 fw-8x: initialize gain properly
2012-11-10 fw-nrw: add charge detection
2012-11-10 fw-8x: sadly disable high gain mode
2012-11-10 fw-8x: add proper blink code
2012-11-19 hw: add note about series-cap
2012-11-24 main: reduce blink intensity
2012-11-24 fw-nrf: jump directly to powerdown after tx
2012-11-25 hw: update hammond libs
2013-01-28 fw-nrw: set PRR
2013-11-04 fw: main: only set value[0]
2013-11-04 fw: use relative link for nrf_frames.h
2013-11-10 fw-nrf: add 12kW defines
2013-11-10 fw-nrf: change default sensor address
2013-11-18 fw-nrf: transmit every second

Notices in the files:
parts and their libraries:
SparkFun: Licensing: CC v3.0 Share-Alike You are welcome to use this library for commercial purposes.
balto: Released under the Creative Commons
balto: http://creativecommons.org/licenses/by-sa/3.0
balto: Released under the Creative Commons Attribution Share-Alike 3.0 License
